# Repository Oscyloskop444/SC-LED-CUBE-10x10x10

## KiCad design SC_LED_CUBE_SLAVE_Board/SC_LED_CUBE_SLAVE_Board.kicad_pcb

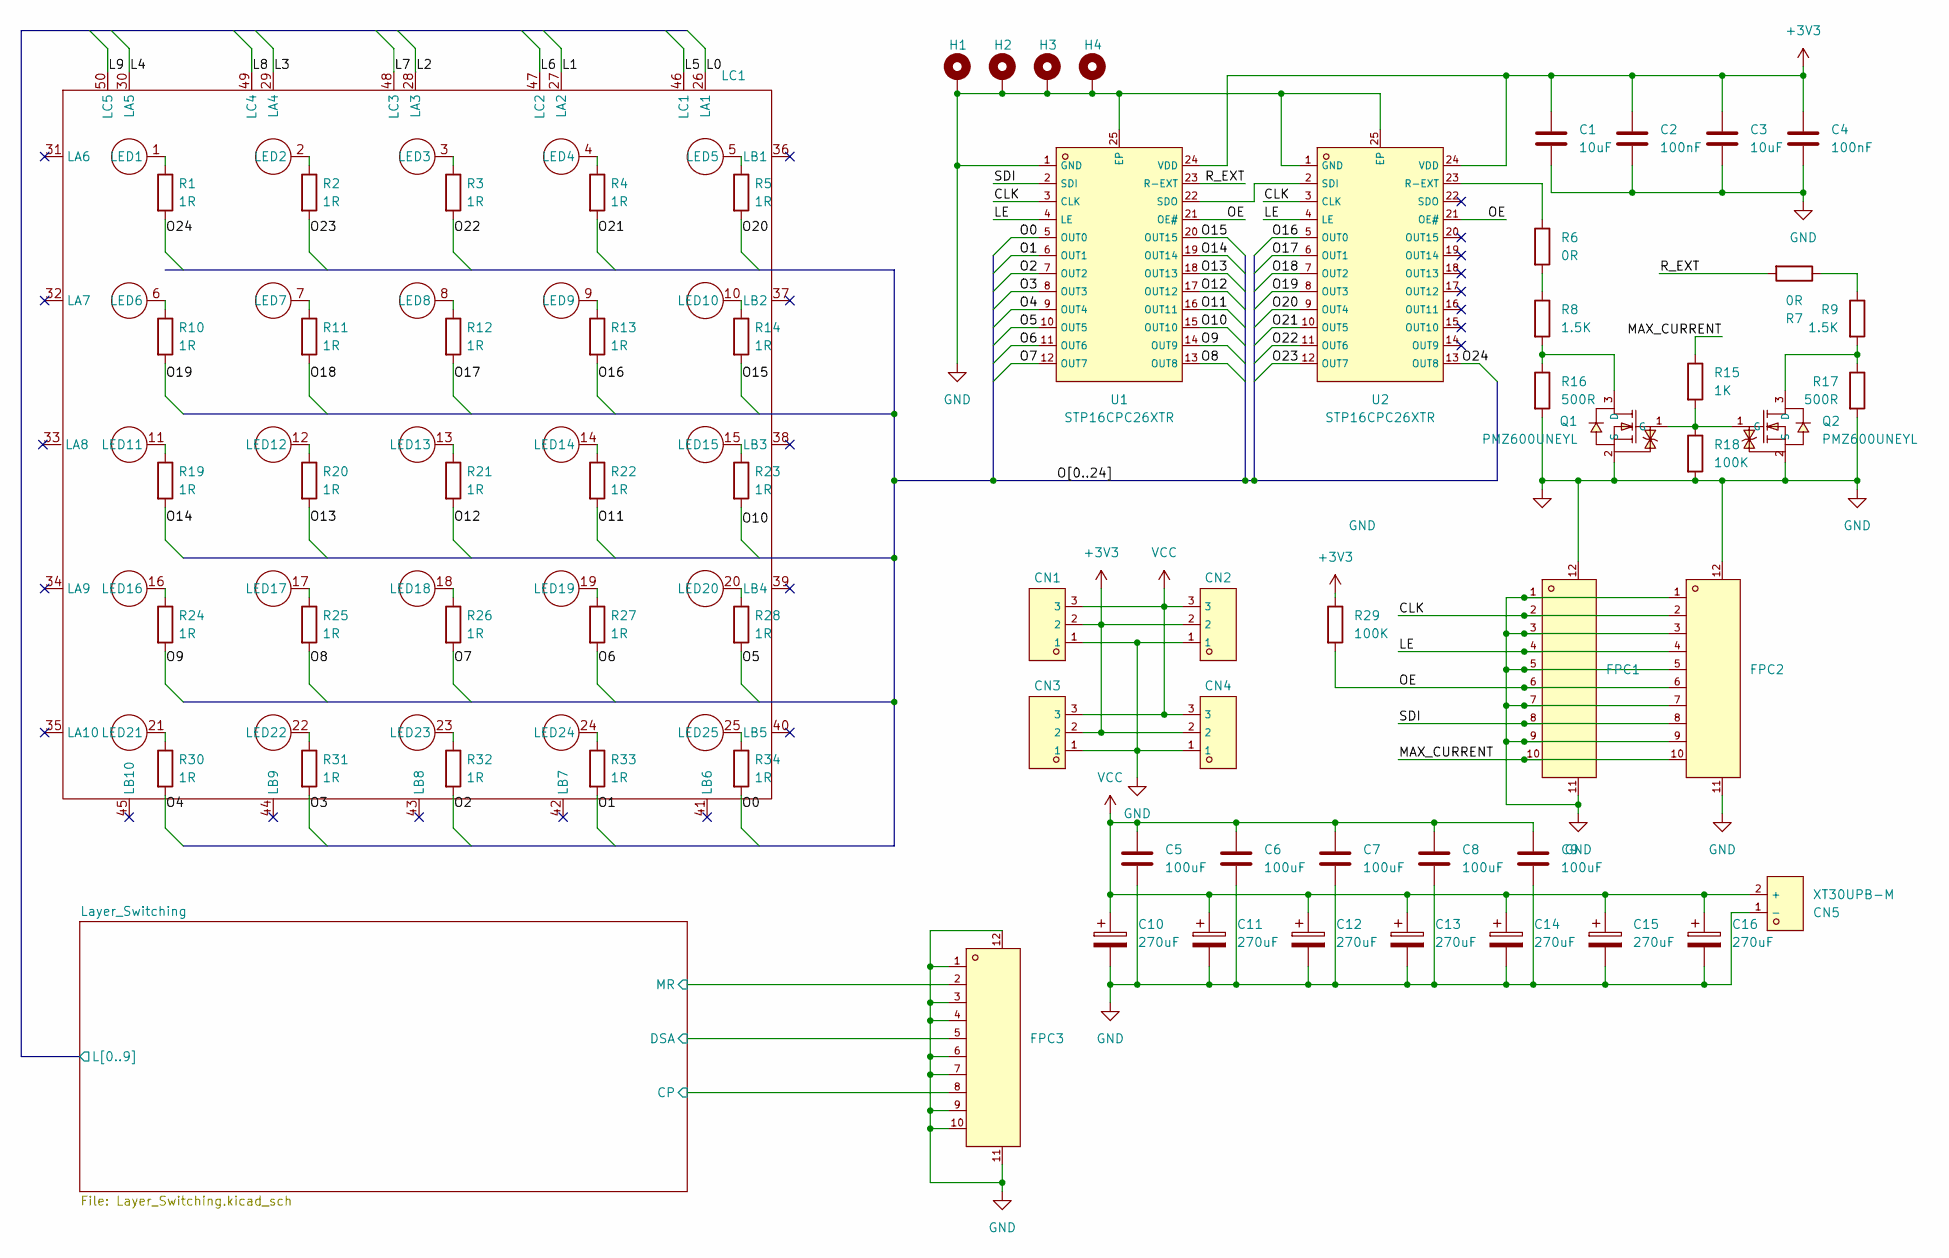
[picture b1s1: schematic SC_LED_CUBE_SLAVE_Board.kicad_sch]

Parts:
C1, C3: 10uF; C_0805_2012Metric_Pad1.18x1.45mm_HandSolder
C2, C4: 100nF; C_0402_1005Metric_Pad0.74x0.62mm_HandSolder
C5, C6, C7, C8, C9: 100uF; C_1206_3216Metric_Pad1.33x1.80mm_HandSolder
C10, C11, C12, C13, C14, C15, C16: 270uF; CP_Radial_D6.3mm_P2.50mm
CN1, CN2, CN3, CN4: B03B-XASK-1-A(LF)(SN); C264992_CONN-TH_B03B-XASK-1-A-LF-SN; LCSC C264992
CN5: XT30UPB-M; C428721_CONN-TH_XT30UPB-M; LCSC C428721
FPC1, FPC2, FPC3: XW05202-100R-00; C2906114_FPC-SMD_10P-P0_50_HCTL_XW05202-100R-00; LCSC C2906114
H1, H2, H3, H4: MountingHole_Pad; MountingHole_3.2mm_M3_Pad_Via
LC1: LED_CUBE_SC
Q1, Q2: PMZ600UNEYL; C547286_SOT-883-3_L1_0-W0_6-BR; LCSC C547286
R1, R2, R3, R4, R5, R10, R11, R12, R13, R14, R19, R20, R21, R22, R23, R24, R25, R26, R27, R28, R30, R31, R32, R33, R34: 1R; R_0402_1005Metric_Pad0.72x0.64mm_HandSolder
R6, R7: 0R; R_0402_1005Metric_Pad0.72x0.64mm_HandSolder
R8, R9: 1.5K; R_0402_1005Metric_Pad0.72x0.64mm_HandSolder
R15: 1K; R_0402_1005Metric_Pad0.72x0.64mm_HandSolder
R16, R17: 500R; R_0402_1005Metric_Pad0.72x0.64mm_HandSolder
R18, R29: 100K; R_0402_1005Metric_Pad0.72x0.64mm_HandSolder
U1, U2: STP16CPC26XTR; C411391_HTSSOP-24_L7_8-W4_4-P0_65-LS6_4-TL-EP; LCSC C411391

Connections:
+3V3: C1.1, C2.1, C3.1, C4.1, CN1.2, CN2.2, CN3.2, CN4.2, R29.1, U1.24 (VDD), U2.24 (VDD); also elsewhere on the board
/CLK: FPC1.2, FPC2.2, U1.3 (CLK), U2.3 (CLK)
/LE: FPC1.4, FPC2.4, U1.4 (LE), U2.4 (LE)
/Layer_Switching/CP: FPC3.8; also elsewhere on the board
/Layer_Switching/DSA: FPC3.5; also elsewhere on the board
/Layer_Switching/L0: LC1.26 (LA1); also elsewhere on the board
/Layer_Switching/L1: LC1.27 (LA2); also elsewhere on the board
/Layer_Switching/L2: LC1.28 (LA3); also elsewhere on the board
/Layer_Switching/L3: LC1.29 (LA4); also elsewhere on the board
/Layer_Switching/L4: LC1.30 (LA5); also elsewhere on the board
/Layer_Switching/L5: LC1.46 (LC1); also elsewhere on the board
/Layer_Switching/L6: LC1.47 (LC2); also elsewhere on the board
/Layer_Switching/L7: LC1.48 (LC3); also elsewhere on the board
/Layer_Switching/L8: LC1.49 (LC4); also elsewhere on the board
/Layer_Switching/L9: LC1.50 (LC5); also elsewhere on the board
/Layer_Switching/MR: FPC3.2; also elsewhere on the board
/MAX_CURRENT: FPC1.10, FPC2.10, R15.1
/O0: R34.2, U1.5 (OUT0)
/O1: R33.2, U1.6 (OUT1)
/O2: R32.2, U1.7 (OUT2)
/O3: R31.2, U1.8 (OUT3)
/O4: R30.2, U1.9 (OUT4)
/O5: R28.2, U1.10 (OUT5)
/O6: R27.2, U1.11 (OUT6)
/O7: R26.2, U1.12 (OUT7)
/O8: R25.2, U1.13 (OUT8)
/O9: R24.2, U1.14 (OUT9)
/O10: R23.2, U1.15 (OUT10)
/O11: R22.2, U1.16 (OUT11)
/O12: R21.2, U1.17 (OUT12)
/O13: R20.2, U1.18 (OUT13)
/O14: R19.2, U1.19 (OUT14)
/O15: R14.2, U1.20 (OUT15)
/O16: R13.2, U2.5 (OUT0)
/O17: R12.2, U2.6 (OUT1)
/O18: R11.2, U2.7 (OUT2)
/O19: R10.2, U2.8 (OUT3)
/O20: R5.2, U2.9 (OUT4)
/O21: R4.2, U2.10 (OUT5)
/O22: R3.2, U2.11 (OUT6)
/O23: R2.2, U2.12 (OUT7)
/O24: R1.2, U2.13 (OUT8)
/OE: FPC1.6, FPC2.6, R29.2, U1.21 (OE#), U2.21 (OE#)
/R_EXT: R7.2, U1.23 (R-EXT)
/SDI: FPC1.8, FPC2.8, U1.2 (SDI)
GND: C1.2, C2.2, C3.2, C4.2, C5.2, C6.2, C7.2, C8.2, C9.2, C10.2, C11.2, C12.2, C13.2, C14.2, C15.2, C16.2, CN1.1, CN2.1, CN3.1, CN4.1, CN5.1 (-), FPC1.1, FPC1.3, FPC1.5, FPC1.7, FPC1.9, FPC1.11, FPC1.12, FPC2.1, FPC2.3, FPC2.5, FPC2.7, FPC2.9, FPC2.11, FPC2.12, FPC3.1, FPC3.3, FPC3.4, FPC3.6, FPC3.7, FPC3.9, FPC3.10, FPC3.11, FPC3.12, H1.1 (1_1), H2.1 (1_1), H3.1 (1_1), H4.1 (1_1), Q1.2 (S), Q2.2 (S), R16.2, R17.2, R18.2, U1.1 (GND), U1.25 (EP), U2.1 (GND), U2.25 (EP); also elsewhere on the board
unnamed: LC1.1 (LED1), R1.1
unnamed: LC1.2 (LED2), R2.1
unnamed: LC1.3 (LED3), R3.1
unnamed: LC1.4 (LED4), R4.1
unnamed: LC1.5 (LED5), R5.1
unnamed: LC1.6 (LED6), R10.1
unnamed: LC1.7 (LED7), R11.1
unnamed: LC1.8 (LED8), R12.1
unnamed: LC1.9 (LED9), R13.1
unnamed: LC1.10 (LED10), R14.1
unnamed: LC1.11 (LED11), R19.1
unnamed: LC1.12 (LED12), R20.1
unnamed: LC1.13 (LED13), R21.1
unnamed: LC1.14 (LED14), R22.1
unnamed: LC1.15 (LED15), R23.1
unnamed: LC1.16 (LED16), R24.1
unnamed: LC1.17 (LED17), R25.1
unnamed: LC1.18 (LED18), R26.1
unnamed: LC1.19 (LED19), R27.1
unnamed: LC1.20 (LED20), R28.1
unnamed: LC1.21 (LED21), R30.1
unnamed: LC1.22 (LED22), R31.1
unnamed: LC1.23 (LED23), R32.1
unnamed: LC1.24 (LED24), R33.1
unnamed: LC1.25 (LED25), R34.1
unnamed: Q1.3 (D), R8.2, R16.1
unnamed: Q1.1 (G), Q2.1 (G), R15.2, R18.1
unnamed: Q2.3 (D), R9.2, R17.1
unnamed: R6.2, R8.1
unnamed: R7.1, R9.1
unnamed: U1.22 (SDO), U2.2 (SDI)
unnamed: R6.1, U2.23 (R-EXT)
VCC: C5.1, C6.1, C7.1, C8.1, C9.1, C10.1, C11.1, C12.1, C13.1, C14.1, C15.1, C16.1, CN1.3, CN2.3, CN3.3, CN4.3, CN5.2 (+); also elsewhere on the board

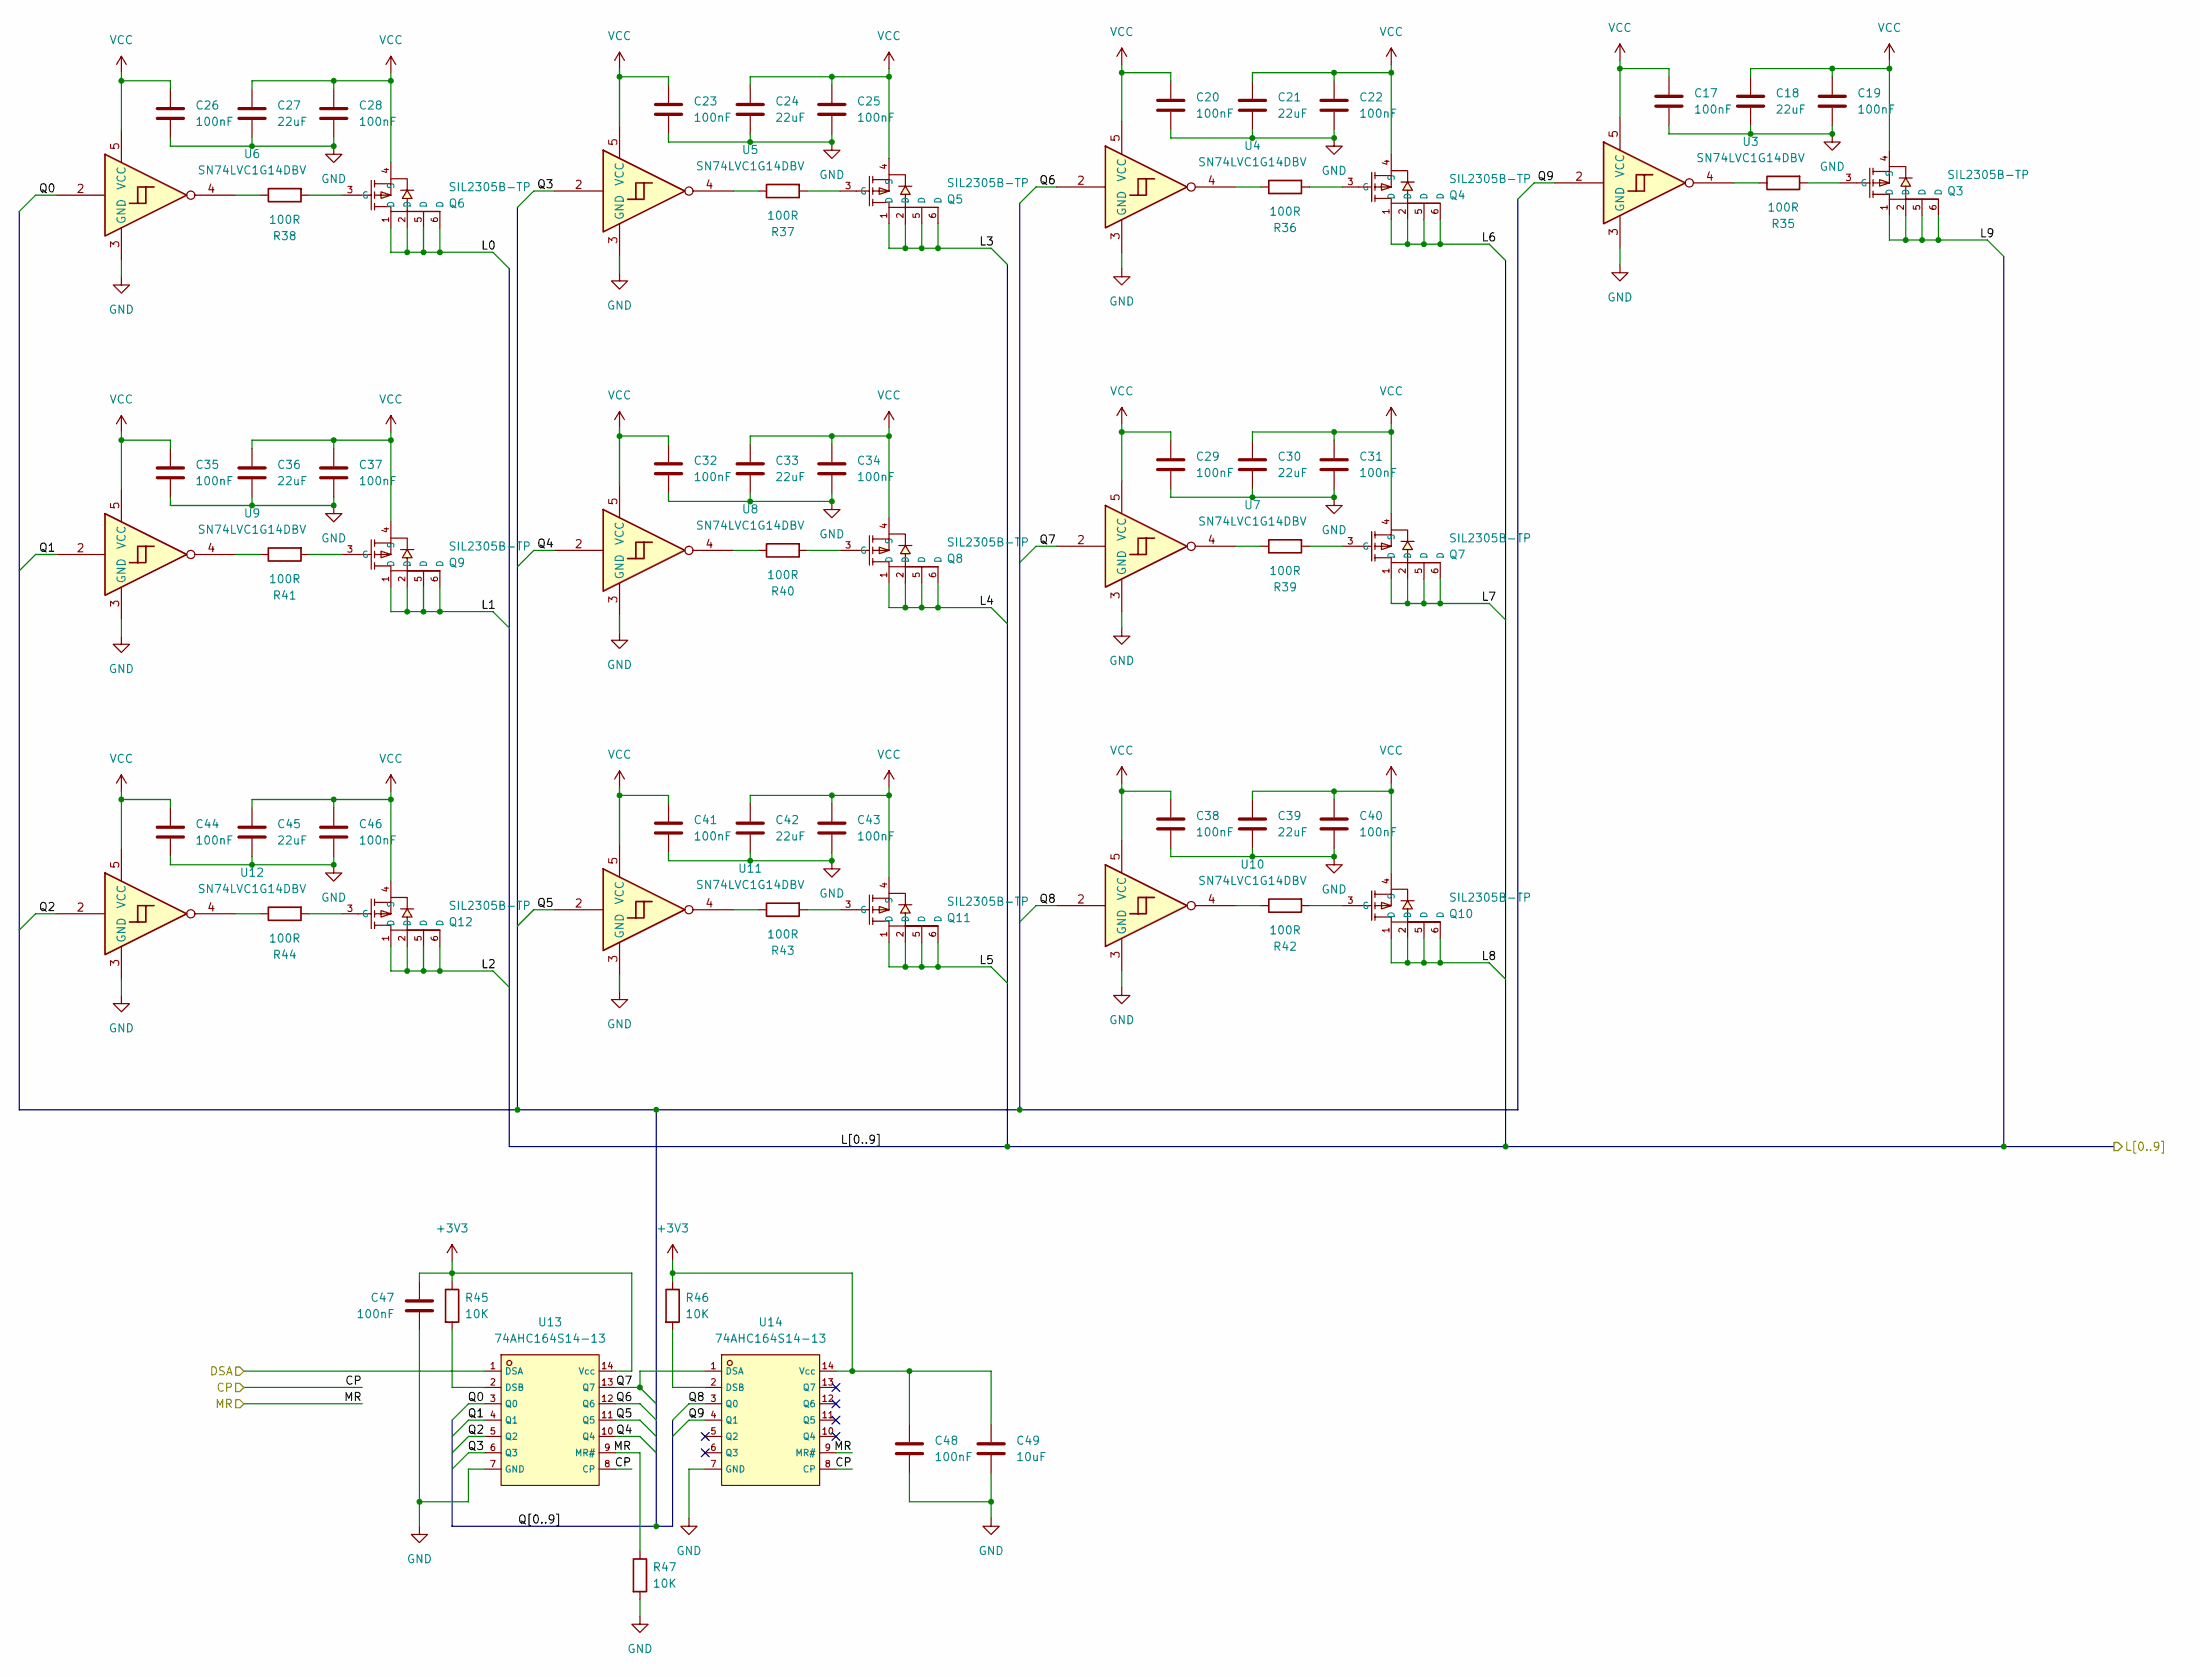
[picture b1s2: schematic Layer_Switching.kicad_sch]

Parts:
C17, C19, C20, C22, C23, C25, C26, C28, C29, C31, C32, C34, C35, C37, C38, C40, C41, C43, C44, C46, C47, C48: 100nF; C_0402_1005Metric_Pad0.74x0.62mm_HandSolder
C18, C21, C24, C27, C30, C33, C36, C39, C42, C45: 22uF; C_0805_2012Metric_Pad1.18x1.45mm_HandSolder
C49: 10uF; C_0805_2012Metric_Pad1.18x1.45mm_HandSolder
Q3, Q4, Q5, Q6, Q7, Q8, Q9, Q10, Q11, Q12: SIL2305B-TP; C3280214_SOT-23-6_L2_9-W1_6-P0_95-LS2_9-BL; LCSC C3280214
R35, R36, R37, R38, R39, R40, R41, R42, R43, R44: 100R; R_0402_1005Metric_Pad0.72x0.64mm_HandSolder
R45, R46, R47: 10K; R_0402_1005Metric_Pad0.72x0.64mm_HandSolder
U3, U4, U5, U6, U7, U8, U9, U10, U11, U12: SN74LVC1G14DBV; SOT-23-5
U13, U14: 74AHC164S14-13; C842271_SO-14_L8_7-W3_9-P1_27-LS6_0-BL; LCSC C842271

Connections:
+3V3: C47.1, C48.1, C49.1, R45.1, R46.1, U13.14 (Vcc), U14.14 (Vcc); also elsewhere on the board
/Layer_Switching/CP: U13.8 (CP), U14.8 (CP); also elsewhere on the board
/Layer_Switching/DSA: U13.1 (DSA); also elsewhere on the board
/Layer_Switching/L0: Q6.1 (D), Q6.2 (D), Q6.5 (D), Q6.6 (D); also elsewhere on the board
/Layer_Switching/L1: Q9.1 (D), Q9.2 (D), Q9.5 (D), Q9.6 (D); also elsewhere on the board
/Layer_Switching/L2: Q12.1 (D), Q12.2 (D), Q12.5 (D), Q12.6 (D); also elsewhere on the board
/Layer_Switching/L3: Q5.1 (D), Q5.2 (D), Q5.5 (D), Q5.6 (D); also elsewhere on the board
/Layer_Switching/L4: Q8.1 (D), Q8.2 (D), Q8.5 (D), Q8.6 (D); also elsewhere on the board
/Layer_Switching/L5: Q11.1 (D), Q11.2 (D), Q11.5 (D), Q11.6 (D); also elsewhere on the board
/Layer_Switching/L6: Q4.1 (D), Q4.2 (D), Q4.5 (D), Q4.6 (D); also elsewhere on the board
/Layer_Switching/L7: Q7.1 (D), Q7.2 (D), Q7.5 (D), Q7.6 (D); also elsewhere on the board
/Layer_Switching/L8: Q10.1 (D), Q10.2 (D), Q10.5 (D), Q10.6 (D); also elsewhere on the board
/Layer_Switching/L9: Q3.1 (D), Q3.2 (D), Q3.5 (D), Q3.6 (D); also elsewhere on the board
/Layer_Switching/MR: R47.1, U13.9 (MR#), U14.9 (MR#); also elsewhere on the board
/Layer_Switching/Q0: U6.2, U13.3 (Q0)
/Layer_Switching/Q1: U9.2, U13.4 (Q1)
/Layer_Switching/Q2: U12.2, U13.5 (Q2)
/Layer_Switching/Q3: U5.2, U13.6 (Q3)
/Layer_Switching/Q4: U8.2, U13.10 (Q4)
/Layer_Switching/Q5: U11.2, U13.11 (Q5)
/Layer_Switching/Q6: U4.2, U13.12 (Q6)
/Layer_Switching/Q7: U7.2, U13.13 (Q7), U14.1 (DSA)
/Layer_Switching/Q8: U10.2, U14.3 (Q0)
/Layer_Switching/Q9: U3.2, U14.4 (Q1)
GND: C17.2, C18.2, C19.2, C20.2, C21.2, C22.2, C23.2, C24.2, C25.2, C26.2, C27.2, C28.2, C29.2, C30.2, C31.2, C32.2, C33.2, C34.2, C35.2, C36.2, C37.2, C38.2, C39.2, C40.2, C41.2, C42.2, C43.2, C44.2, C45.2, C46.2, C47.2, C48.2, C49.2, R47.2, U3.3 (GND), U4.3 (GND), U5.3 (GND), U6.3 (GND), U7.3 (GND), U8.3 (GND), U9.3 (GND), U10.3 (GND), U11.3 (GND), U12.3 (GND), U13.7 (GND), U14.7 (GND); also elsewhere on the board
unnamed: Q3.3 (G), R35.2
unnamed: Q4.3 (G), R36.2
unnamed: Q5.3 (G), R37.2
unnamed: Q6.3 (G), R38.2
unnamed: Q7.3 (G), R39.2
unnamed: Q8.3 (G), R40.2
unnamed: Q9.3 (G), R41.2
unnamed: Q10.3 (G), R42.2
unnamed: Q11.3 (G), R43.2
unnamed: Q12.3 (G), R44.2
unnamed: R35.1, U3.4
unnamed: R36.1, U4.4
unnamed: R37.1, U5.4
unnamed: R38.1, U6.4
unnamed: R39.1, U7.4
unnamed: R40.1, U8.4
unnamed: R41.1, U9.4
unnamed: R42.1, U10.4
unnamed: R43.1, U11.4
unnamed: R44.1, U12.4
unnamed: R45.2, U13.2 (DSB)
unnamed: R46.2, U14.2 (DSB)
VCC: C17.1, C18.1, C19.1, C20.1, C21.1, C22.1, C23.1, C24.1, C25.1, C26.1, C27.1, C28.1, C29.1, C30.1, C31.1, C32.1, C33.1, C34.1, C35.1, C36.1, C37.1, C38.1, C39.1, C40.1, C41.1, C42.1, C43.1, C44.1, C45.1, C46.1, Q3.4 (S), Q4.4 (S), Q5.4 (S), Q6.4 (S), Q7.4 (S), Q8.4 (S), Q9.4 (S), Q10.4 (S), Q11.4 (S), Q12.4 (S), U3.5 (VCC), U4.5 (VCC), U5.5 (VCC), U6.5 (VCC), U7.5 (VCC), U8.5 (VCC), U9.5 (VCC), U10.5 (VCC), U11.5 (VCC), U12.5 (VCC); also elsewhere on the board

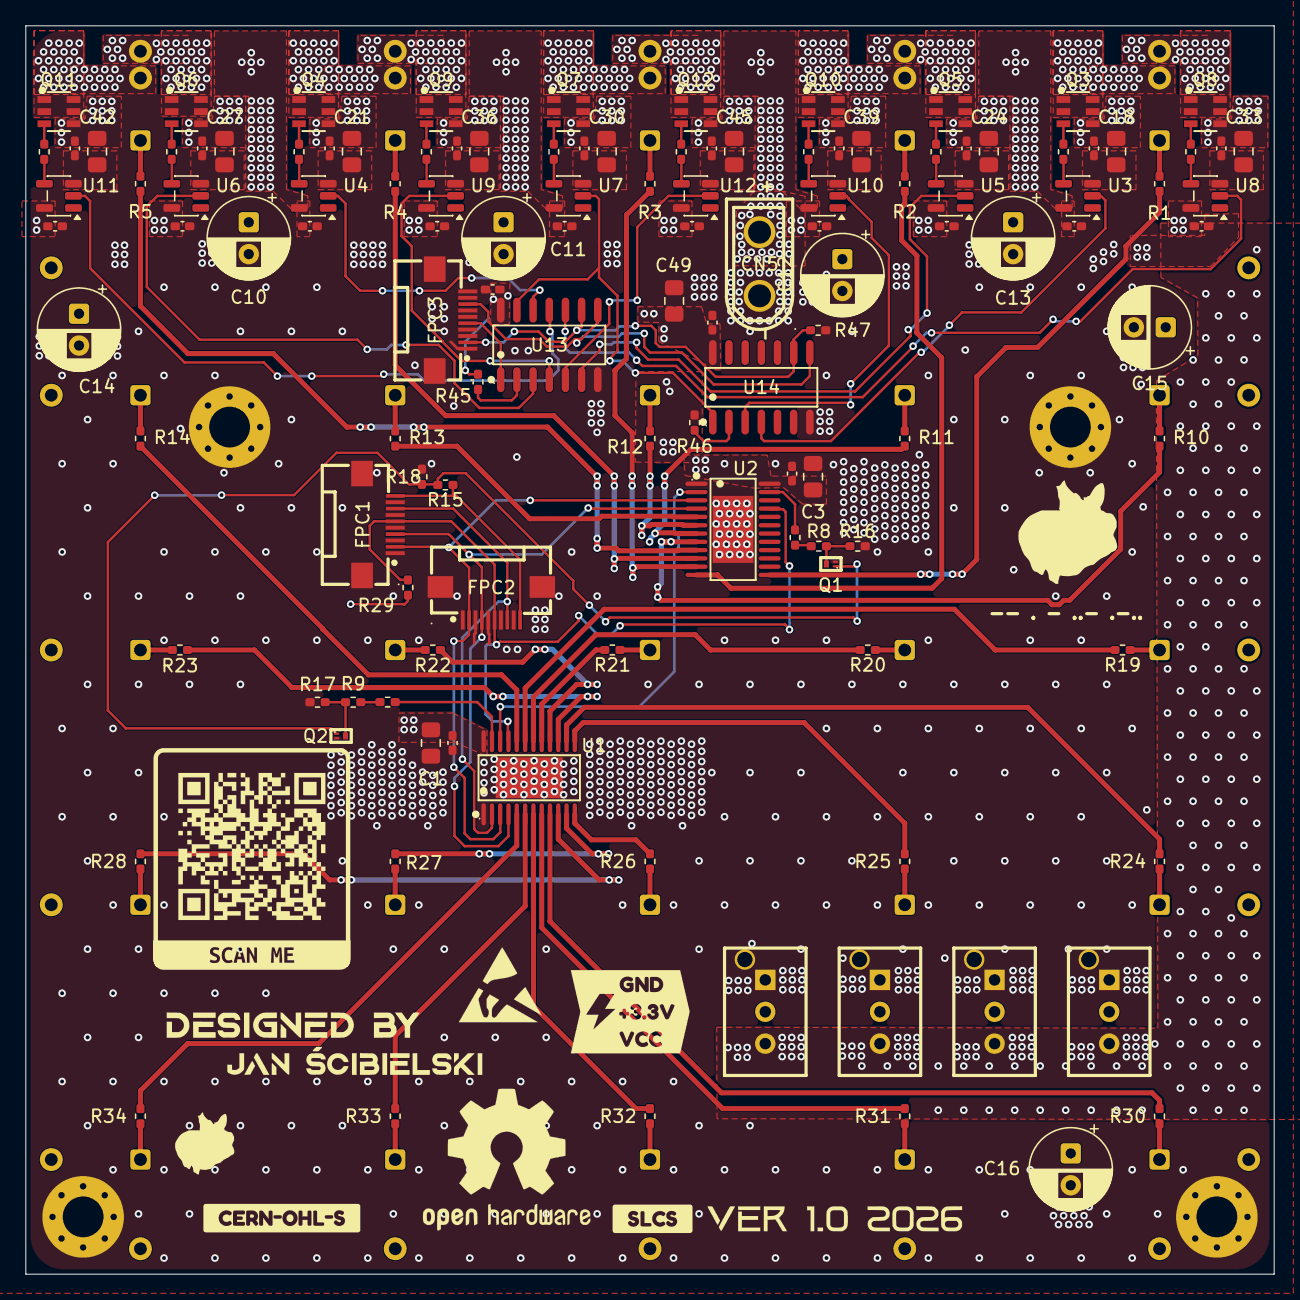
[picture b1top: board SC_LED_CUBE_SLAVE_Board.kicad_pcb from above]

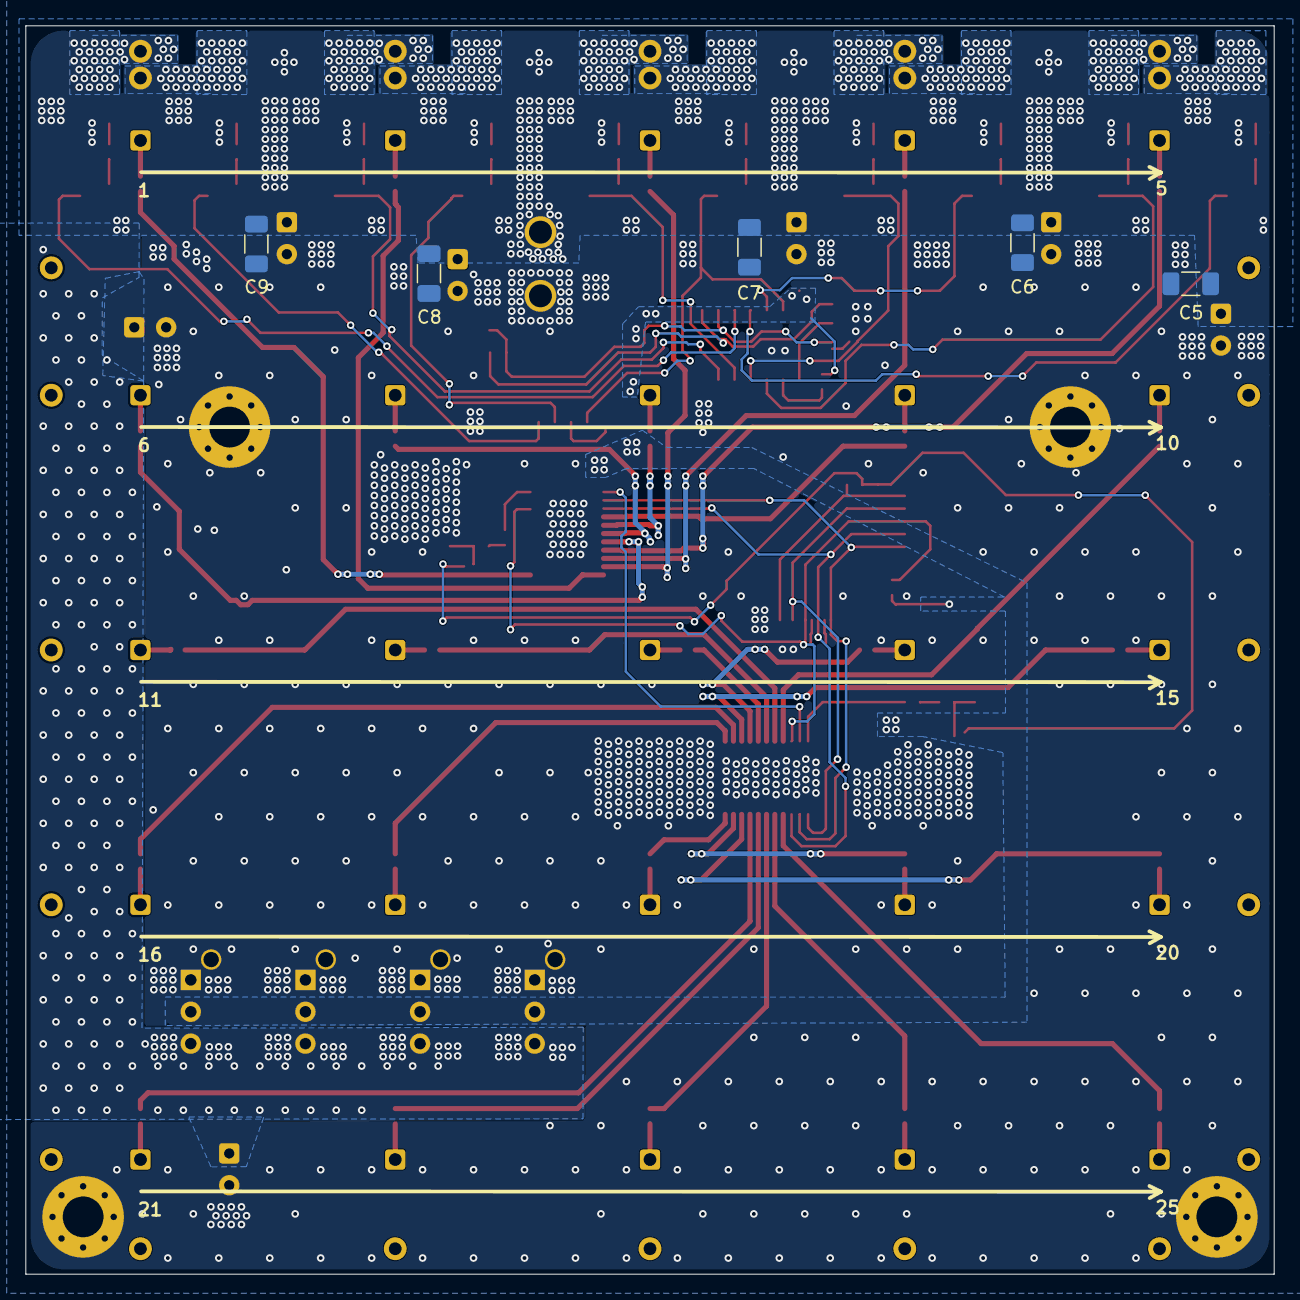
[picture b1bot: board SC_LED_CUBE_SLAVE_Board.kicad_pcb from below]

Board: 2 copper layers, 98.0 x 98.0 mm, 139 parts (6 on the bottom side), 111 nets.

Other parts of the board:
kobee-studio-6AA935D6: Kobee Studio; kobee-studio-6AA935D6
kobee-studio-6AA936F7: Kobee Studio; kobee-studio-6AA9368C
kobee-studio-6AA92370: Kobee Studio; kobee-studio-6AA92370
kobee-studio-6AA93567: Kobee Studio; kobee-studio-6AA93567

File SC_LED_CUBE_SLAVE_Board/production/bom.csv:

Designator,Footprint,Quantity,Value,LCSC Part #
"C1, C3, C49",0805,3,10uF,
"C10, C11, C12, C13, C14, C15, C16",CP_Radial_D6.3mm_P2.50mm,7,270uF,
"C17, C19, C2, C20, C22, C23, C25, C26, C28, C29, C31, C32, C34, C35, C37, C38, C4, C40, C41, C43, C44, C46, C47, C48",0402,24,100nF,
"C18, C21, C24, C27, C30, C33, C36, C39, C42, C45",0805,10,22uF,
"C5, C6, C7, C8, C9",1206,5,100uF,
"CN1, CN2, CN3, CN4",C264992_CONN-TH_B03B-XASK-1-A-LF-SN,4,B03B-XASK-1-A(LF)(SN),C264992
CN5,C428721_CONN-TH_XT30UPB-M,1,XT30UPB-M,C428721
"FPC1, FPC2, FPC3",C2906114_FPC-SMD_10P-P0_50_HCTL_XW05202-100R-00,3,XW05202-100R-00,C2906114
LC1,LED_CUBE_SC,1,~,
"Q1, Q2",C547286_SOT-883-3_L1_0-W0_6-BR,2,PMZ600UNEYL,C547286
"Q10, Q11, Q12, Q3, Q4, Q5, Q6, Q7, Q8, Q9",C3280214_SOT-23-6_L2_9-W1_6-P0_95-LS2_9-BL,10,SIL2305B-TP,C3280214
"R1, R10, R11, R12, R13, R14, R19, R2, R20, R21, R22, R23, R24, R25, R26, R27, R28, R3, R30, R31, R32, R33, R34, R4, R5",0402,25,1R,
R15,0402,1,1K,
"R16, R17",0402,2,500R,
"R18, R29",0402,2,100K,
"R35, R36, R37, R38, R39, R40, R41, R42, R43, R44",0402,10,10R,
"R45, R46, R47",0402,3,10K,
"R6, R7",0402,2,0R,
"R8, R9",0402,2,1.5K,
"U1, U2",C411391_HTSSOP-24_L7_8-W4_4-P0_65-LS6_4-TL-EP,2,STP16CPC26XTR,C411391
"U10, U11, U12, U3, U4, U5, U6, U7, U8, U9",SOT-23-5,10,SN74LVC1G14DBV,
"U13, U14",C842271_SO-14_L8_7-W3_9-P1_27-LS6_0-BL,2,74AHC164S14-13,C842271
